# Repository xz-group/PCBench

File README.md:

# PCBench

PCBench is a free open-source benckmark for board-level hardware attacks and Trojans.

## What's News

Version 1.0

This is the initial release of the benchmars for board-level hardware security.

## Motivation
Most modern electronic systems are hosted by printed circuit boards(PCBs), making them a ubiquitous system component that can take many different shapes and forms. In order to achieve a high level of economy of scale, the global supply chain of electronic systems has evolved into disparate segments for the design, fabrication, assembly, and testing of PCB boards and their various associated components. <br />
As a consequence, the modern PCB supply chain exposes many vulnerabilities along its different stages, allowing adversaries to introduce malicious alterations to facilitate board-level attacks. As an emerging hardware threat, the attack and defense techniques at the board level have not yet been systemically explored and thus require a thorough and comprehensive investigation. <br />
In the absence of a standard board-level attack benchmark, current re-search on perspective countermeasures is likely to be evaluated on proprietary variants of ad-hoc attacks, preventing credible and verifiable comparison among different techniques. Upon this request, we have created the PCBench, which is a set of board-level attack benchmarks for open-source release.

## Benchmarking Methodology

We generated the benchmarks based on the methodology proposed in our **ASP-DAC 2021 paper: *[PCBench: Benchmarking of Board-Level Hardware Attacks and Trojans](http://jin.ece.ufl.edu/papers/ASPDAC2021_PCB.PDF)***.
In this paper, we systematically defined and categorized a broad range of board-level attacks. 
For the first time, the attack vectors and construction rules for board-level attacks were developed.
A practical and reliable board-level attack benchmark generation scheme was also developed, which can be used to produce references for evaluating countermeasures.

## Released Benchmarks
To facilitate the development of board-level attack benchmarks, representative circuit boards are chosen as the victim designs. 
Open-source hardware projects are mainly selected due to their modern design styles, the availability of PCB designs as well as detailed documents, firmware, and/or application software. 
As a result, researchers can easily reconstruct the board-level security evaluation benchmarks. 

**The following table lists the released benchmarks:**

 Design Name | Description | Dimension (mm^2) | No. of Components | No. of Layers
 ----------- | ----------- | :---------: | :-----------------: | :-------------:
 [arduino-due](arduino-due) | Microcontroller devlopment board based on ATsam3x8e with ARM Cortex-M3 core | 102x53 | 141 | 2
 [a13-olinuxino](a13-olinuxino-g2) | Single-board Linux computer based on Allwinner-A13 with Cortex-A8 core | 120x120|370|4

*This is not the full list of benchmarks as we continue developing the new benchmarks.* 

The fabricated Arduino-due board with and without Trojans are shown below.

## Contributiors
The PCBench is mainly developed by *Huifeng Zhu* and *[Dr.Silvia Zhang](https://xzgroup.wustl.edu/people/xuan-silvia-zhang/)* from *Washington University in St.Louis*; *[Dr.Yier Jin](http://jin.ece.ufl.edu/)* from the *University of Florida*; and *[Dr.Xiaolong Guo](https://www.ece.k-state.edu/people/faculty/guo/)* from *Kansas State University*.

We also appreciate the efforts of below contributors: 

## How to Refer to PCBench?
If you are using the benchmarks provided in PCBench to develop either threat mitigation methods or new threat exploitations, please cite our official paper of PCBench. 
You can find the paper in the website of IEEE: [link]() or at [link](http://jin.ece.ufl.edu/papers/ASPDAC2021_PCB.PDF).

A typical BibTeX citation would be, for example:
```
@software{PCBench,
  author = {Huifeng Zhu and Xiaolong Guo and Yier Jin and Xuan Zhang}, % actual author and maintainer
  title = {PCBench: Benchmarking of Board-Level Hardware Attacks and Trojans},
  booktitle = {26th Asia and South Pacific Design Automation Conference (ASP-DAC)},
  year = {2021},
  url = {https://github.com/xz-group/PCBench},
  version = {1.0},
  date = {2020-10-15}, % set to the release date
}
```
## Get Feedback
Feel free to contact us if you have questions about PCBench: **Huifeng Zhu (zhuhuifeng@wustl.edu)**.

## License

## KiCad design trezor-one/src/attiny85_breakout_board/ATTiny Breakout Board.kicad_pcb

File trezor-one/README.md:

# Trezor One Benchmark

https://trezor.io/

## High-level Description of Hardware Attack
The goal of the Trezor One Benchmark is to siphon the recovery seed from a Trezor One device. This information could then be used to retrieve the original cryptocurrency passwords stored by the user. The recovery process is used in the event that the user forgets their PIN number or enters too many incorrect attempts. The user manual outlines this [recovery process](https://wiki.trezor.io/User_manual:Recovery).

During the initial startup sequence of the Trezor One, the user is instructed to write down a unique, device-generated sequence of 24 english words. Each word is displayed one at a time on the Trezor's built-in monochrome display.

This attack describes the necessary steps for capturing packets of display data and decoding them to reveal the full recovery seed.

## Data Capture
The Trezor One Victim board is equipped with a malicious ATtiny microcontroller that is attached, in a slave configuration, to the Trezor's STM32 microcontroller SPI lines. These SPI lines are also connected the the Trezor's display and are used to send bitmap image data. This configuration allows the malicious ATtiny to go undetected while still having access to all data being sent from the Trezor's microcontroller to its display.

Due to how the display operates, the Trezor's microcontroller sends a complete bitmap image to the display each time it needs to be altered, regardless of how many pixels need to change. This is beneficial because it makes it easy to decode recorded SPI packets and rebuild them into complete images. These decoded images represent exactly, pixel for pixel, what was displayed on the Trezor device at the time of packet transmission.

## Implementing the Attack

### Technical Details

#### Display Connecter Pins Table:

| PIN | <------------> | NET |
| ----------- | ----------- | ----------- |
| 12 | <------------> | GND |
| 13 | <------------> | SPI ENABLE |
| 15 | <------------> | DISPLAY DATA/COMMAND |
| 18 | <------------> | SPI CLOCK |
| 19 | <------------> | SPI DATA |

#### Trezor SSD1306 Operation
The display used is a 128x64 OLED SPI display. Internally, the display contains a single-chip driver called the SSD1306 which is widely utilized and documented. The full details of the [SSD1306 documentation](https://cdn-shop.adafruit.com/datasheets/SSD1306.pdf) are crucial to gaining a low-level understanding of this attack. 

A full screen's worth of data is sent to the display each time it is updated. At a simple level, there are 8,192 total pixels and each pixel is driven by a 1 for ON or 0 for OFF. This series of 1024 1's and 0's are sent one byte at a time via SPI to the display. However, they are not ordered left to right and top to bottom as one might expect. The full details of the pixel mapping algorithm is outlined on page 25 of the [SSD1306 documentation](https://cdn-shop.adafruit.com/datasheets/SSD1306.pdf) with regards to the display's GDDRAM. This process needs to be reversed for decoding and is exactly what is embedded in the [src/image_builder.py](image_builder.py) script.

Along with the 8,192 data bits that are sent to the display, there are also command sequences that are sent at the beginning of each transmission that do not represent pixel values. Outlined below is information representing the series of bits sent via SPI to the display by the Trezor. If necessary, specific command bytes can be tracked down in the [Trezor Firmware](https://github.com/trezor/trezor-mcu).

* **Setup Command Bytes (25 total)**
    * Description: The setup command bytes are sent directly after the RESET line of the display is triggered on startup. They aid in resetting the display, setting the contrast, setting the page addressing mode, etc. The exact bytes and corresponding meaning can be found in the [oled.c](https://github.com/trezor/trezor-mcu/blob/8af1f3643651e1cbee6b6196401f9c63e7cfc0f9/oled.c) file in the [Trezor Firmware](https://github.com/trezor/trezor-mcu).
    * Data: {0xAE, 0xD5, 0x80, 0xA8, 0x3F, 0xD3, 0x00, 0x40, 0x8D, 0x14, 0x20, 0x00, 0xA1, 0xC8, 0xDA, 0x12, 0x81, 0xCF, 0xD9, 0xF1, 0xDB, 0x40, 0xA4, 0xA6, 0xAF}
* **Prepended Command Bytes (3 total)**
    * Description: The prepended command bytes are sent directly before new image data is sent. For the Trezor, these bytes are always the same and can be helpful as a delimiter for debugging purposes.
    * Data: {0x00, 0x10, 0x40}
* **Pixel Value Bytes (1024 total)**
* Description: The pixel value bytes represent 1's and 0's for each of the 8,192 pixels. This means that there are 1024 SPI byte packets sent for this part of the transmission. This is the most important part of the transmission for the attack and is the only piece that needs to be recorded to EEPROM since the other pieces are constant and predictable.
* Data: {0x__, 0x__, 0x__, .......}

It is important to note that there is a signal connected to the display (DISPLAY DATA/COMMAND or D/C) that tells the display whether the incoming data is a series of command bytes or data bytes. For the Setup and Prepended Command Bytes, the D/C pin is pulled low so that the data is transferred to the SSD1306 command register. For the Pixel Value Bytes, the D/C is pulled high to be treated as data.

The order in which these command bytes and data bytes are sent is consistent:
1. The Setup Command Bytes are sent only once when the device is powered on.
1. The Preprended Command Bytes are sent before the initial screen data is sent.
1. The Pixel Value Bytes are sent as 0's (1024 bytes of 0x00) to clear the GDDRAM of the SSD1306.
1. The Preprended Command Bytes are sent before the startup screen data is sent.
1. The Pixel Value Bytes are sent to display the startup screen.
1. The previous two steps are repeated for every subsequent image displayed. This means that subsequent transmissions are a total of 1027 bytes (3 Prepend Command Bytes + 1024 Pixel Value Bytes)

Manual tests with an Arduino board and an external 128x64 OLED SPI display can be used to test what unique outputs may look like. Modify [SPI_Manual_Test.ino](/src/SPI_Manual_Test/SPI_Manual_Test.ino) for testing.

### Ideal Attack Sequence
1. Program the malicious ATtiny chip with firmware that enables it to record and store SPI packets to EEPROM.
1. After Trezor device is setup and functional, the malicious ATtiny chip will contain the SPI packets relating to the recovery seed image data. This means that the ATtiny device can now be connected to in some fashion that allows for its EEPROM to be extracted.
1. Enter the extracted EEPROM bytes into a .csv file.
1. Run the image builder Python script that converts the data in the .csv file to a .png image.
1. Repeat the previous step until all images representing each word in the recovery seed are created.
1. Use the recovery seed to gain access to the information on the Trezor device by following the [recovery process](https://wiki.trezor.io/User_manual:Recovery).

### Proof of Concept Attack Sequence
To prove that this ideal attack sequence is possible, various methods and tools were used to extract test data from a from both a real Trezor One and a Trezor victim board.

First, a Trezor victim board was populated. Firmware was built and uploaded by following the [Trezor One Dev Kit](https://mcudev.github.io/trezor-dev-kit/) documentation. Once the device is set up, you must navigate to trezor.io/start and follow the instructions. Unfortunately, this process involves updating the firmware which seems to halt any progress past this point. After the forced update, the Trezor displays an "Unknown bootloader detected" warning and does not work. However, for the purposes of the proof of concept, this limitation was ignored because the SPI data packets used to display the startup screen and "Unknown bootloader detected" warning are of the same format as the packets used to display all content (including the recovery seed words).

Next, a logic analyzer was connected to the necessary pins on the display connector (see Technical Details) using an improvised connector. The HEX values sent over the SPI data line were then exported to the [startup_spi_data.csv](src/startup_spi_data.csv) file. The beginning and ending of the 1024 bytes representing each displayed image were then set manually in the [image_builder.py](src/image_builder.py) file. At this point in testing, the Trezor victim board displayed two images on startup. The first was a lock icon and the second was the "Unknown bootloader detected" warning. Setting and running the python script for both sets of 1024 bytes in the .csv file resulted in the [Lock Screen Image](src/lock_screen.png) and [Info Screen Image](src/info_screen.png) being generated.

To prove that these results were relevant to a real Trezor, the improvised connector was placed on a geniune Trezor One. Using a logic analyzer in the same fashion resulted in the [real_trezor_startup.csv](src/real_trezor_startup.csv) file. After setting the start and end rows of the SPI data relating to the startup screen, the python script produced the [real_trezor_startup.png](src/real_trezor_startup.png) image.

### Further Implementation

Currently, there is one gap between the proof of concept and the ideal attack sequence. In the proof of concept, the SPI data was captured with a logic analyzer and then exported to .csv file. In the ideal attack sequence, the ATtiny captures the data and the user then connects to the ATtiny to extract the recorded data from EEPROM.

Firmware for the ATtiny needs to be written that implements it as an SPI slave. Since the general purpose SPI library does not support the ATtiny85 being used, a more primitive script must be used. Refer to this [stackexchange post](https://electronics.stackexchange.com/questions/60114/spi-h-for-attiny) for ideas.

Once this is implemented, the next immediate problem is EEPROM space. It must be noted that the data has to be held in EEPROM because it needs to be stored in non-volatile memory. The Trezor will be powered off before the data extraction from the ATtiny occurs. It seems that the ATtiny85 has 512 bytes of EEPROM. Unfortunately, this is nowhere near sufficient for this application. Ideally, 24,576 bytes (24 recovery screens * 1024 bytes per display image) would be available to record the SPI data to. This also assumes that the ATtiny is equipped with code that knows exactly which SPI packets will represent the 24 recovery screens that need to be recorded. On the surface, this may seem simple to account for. In the startup sequence, the recovery screens should always be the Nth screen to be displayed. The ATtiny would then be able to count packets until it gets to the Nth screen. However, this may not work because of variants such as the unnecessary button presses from the user that result in extra screens being displayed. Therefore, a better method will probably have to be utilized. One method would be to figure out if the recovery screens have a special, unique design. For example, as shown in this [photo](trezor-one-confirm-seed.jpeg), the ATtiny could be programmed with a bitmap that has the correct bytes representing "Write down the seed" and "Nth word is:." These could then be compared with the most recently recorded packet to decide whether or not the packet represent a recovery screen. Furthermore, this method can also help reduce necessary EEPROM space. It can be noted than in the [photo](trezor-one-confirm-seed.jpeg), takes up at most 1/3 of the vertical space and slightly more than 1/2 of the horizontal space. While this can't solve the 512 byte limitation, it can greatly reduce the EEPROM size needed to well under 24,576 bytes. Since the final EEPROM size needed will be greater than the currently available 512 bytes in the ATtiny85, there are two options. The first is to choose another microcontroller with a larger EEPROM. The second option would be to add an external EEPROM chip which is cheap and offers a tremendous amount of storage. However, one caveat of the latter method is that the external EEPROM would need to be connected over SPI. This may potentially pose a problem because the microcontroller would have to act as both and SPI slave for the STM32 and a master for the external EEPROM.

### ATtiny85-20M1 Breakout Board

In order to upload code to this ATtiny85 package for testing, a custom breakout board is needed. This is because the footprint is unique and compatible breakout boards are difficult to find online. This breakout board was designed in KiCad and an image of the board along with the pinout information is listed below. All design files can be found [here](attiny85_breakout_board).

| Header Pin | ATtiny85 Pin | Connection |
| ----------- | ----------- | ----------- |
| 1 | 1 | RESET/PB5 |
| 2 | 2 | XTAL1/PB3 |
| 5 | 5 | XTAL2/PB4 |
| 8 | 8 | GND |
| 11 | 11 | AREF/PB0 |
| 12 | 12 | PB1 |
| 14 | 14 | PB2 |
| 15 | 15 | VCC |

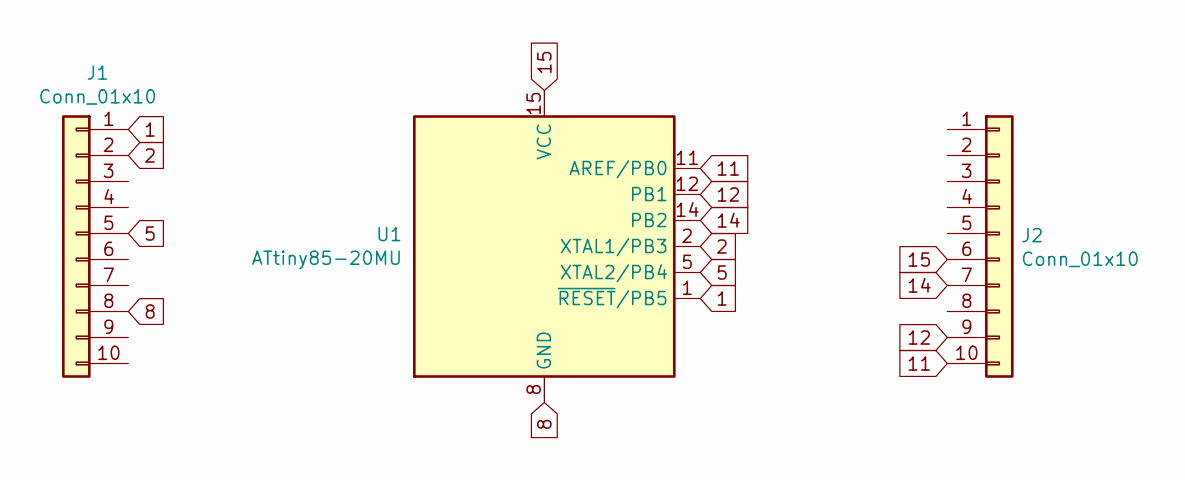
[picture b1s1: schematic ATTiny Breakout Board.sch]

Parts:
J1, J2: Conn_01x10; PinHeader_1x10_P2.54mm_Vertical
U1: ATtiny85-20MU; QFN-20-1EP_4x4mm_P0.5mm_EP2.6x2.6mm

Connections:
1: J1.1, U1.1 (~RESET~/PB5)
2: J1.2, U1.2 (XTAL1/PB3)
5: J1.5, U1.5 (XTAL2/PB4)
8: J1.8, U1.8 (GND), U1.21 (GND)
11: J2.10, U1.11 (AREF/PB0)
12: J2.9, U1.12 (PB1)
14: J2.7, U1.14 (PB2)
15: J2.6, U1.15 (VCC)
unnamed: J1.3, U1.3 (NC)
unnamed: J1.4, U1.4 (NC)
unnamed: J1.6, U1.6 (NC)
unnamed: J1.7, U1.7 (NC)
unnamed: J1.9, U1.9 (NC)
unnamed: J1.10, U1.10 (NC)
unnamed: J2.1, U1.20 (NC)
unnamed: J2.2, U1.19 (NC)
unnamed: J2.3, U1.18 (NC)
unnamed: J2.4, U1.17 (NC)
unnamed: J2.5, U1.16 (NC)
unnamed: J2.8, U1.13 (NC)

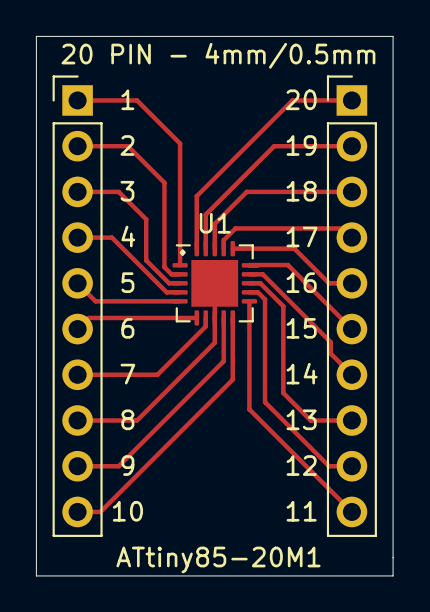
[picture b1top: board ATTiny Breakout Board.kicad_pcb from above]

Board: 2 copper layers, 19.8 x 30.0 mm, 3 parts (0 on the bottom side), 20 nets.

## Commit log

2020-10-16 arduino image
2020-10-16 Upload arduino due CAM
2020-11-19 Upload the benchmark of a13-olinuxino board.
2021-09-22 Update the schematic, layout, and test results of Arduino due
2021-09-22 Update the schematic and layout of 13
2021-09-22 trezor_one benchmark
2021-09-22 fix the links
